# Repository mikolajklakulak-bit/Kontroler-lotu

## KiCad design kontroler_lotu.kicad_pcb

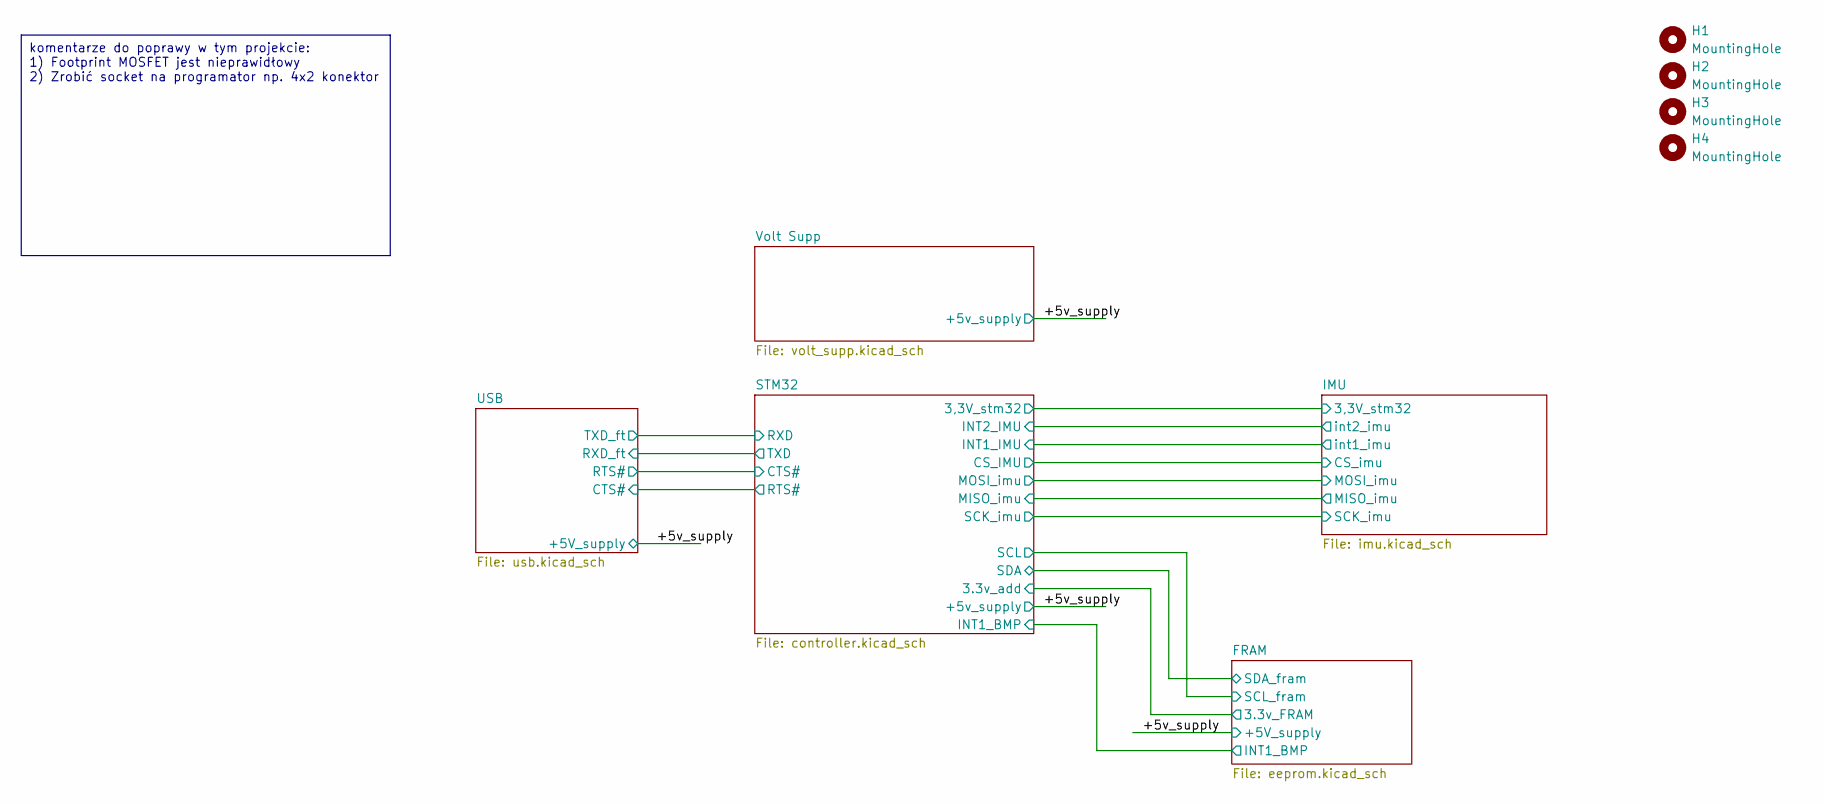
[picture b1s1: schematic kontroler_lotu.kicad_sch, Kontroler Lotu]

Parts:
H1, H2, H3, H4: MountingHole; MountingHole_3.2mm_M3_Pad

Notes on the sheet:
komentarze do poprawy w tym projekcie: 1) Footprint MOSFET jest nieprawidłowy 2) Zrobić socket na programator np. 4x2 konektor

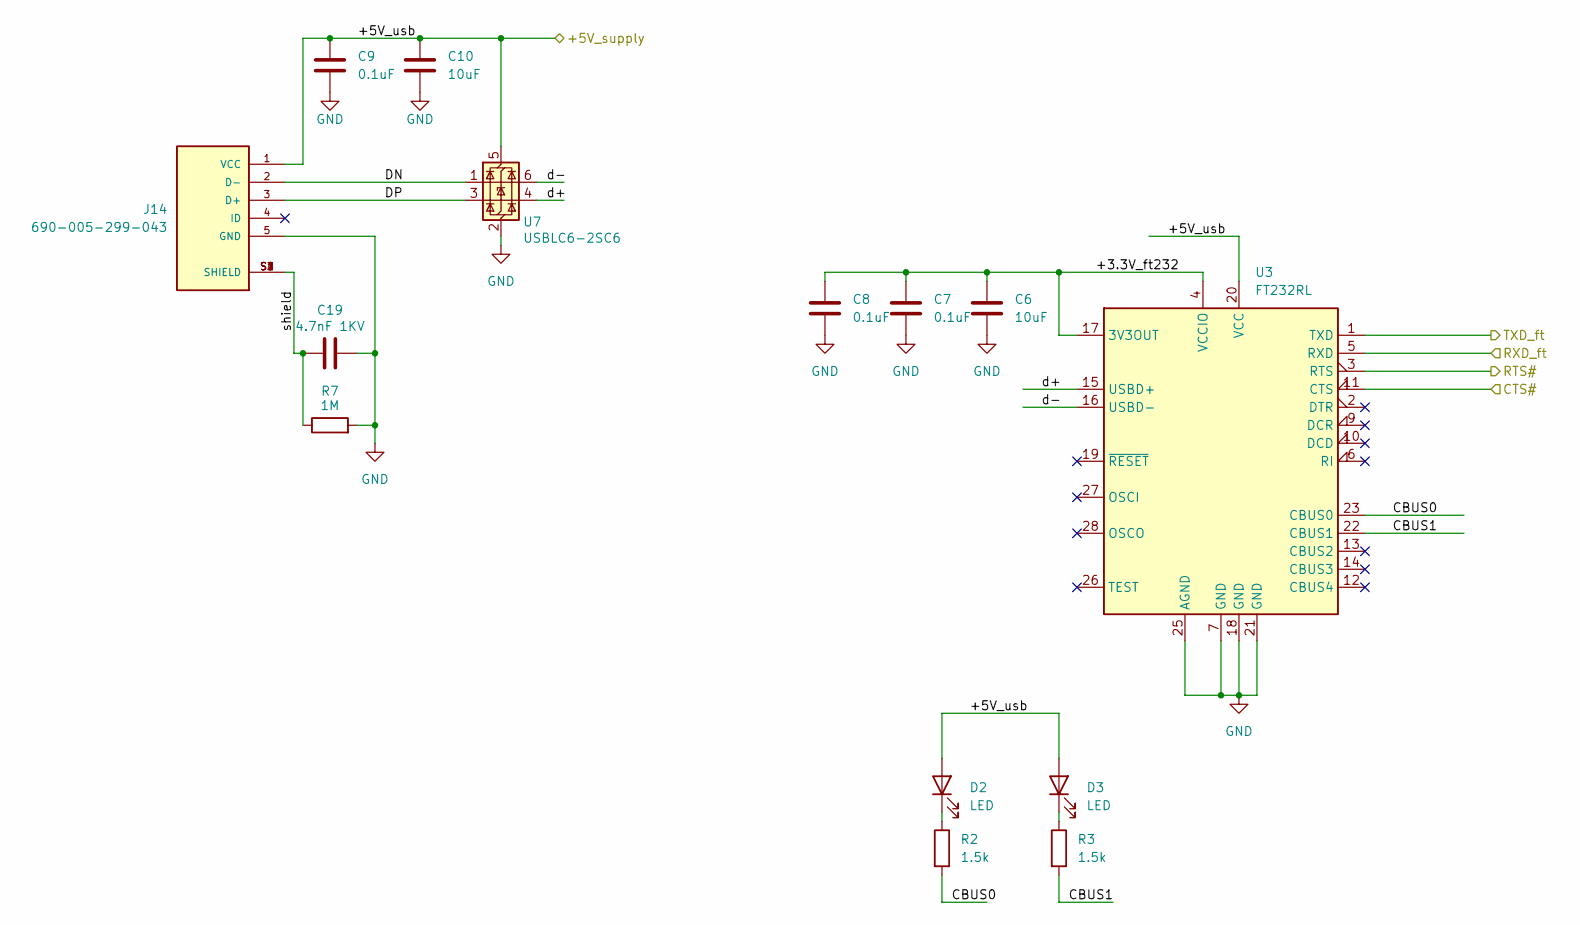
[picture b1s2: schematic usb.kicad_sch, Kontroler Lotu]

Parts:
C6, C10: 10uF; C_1206_3216Metric
C7, C8, C9: 0.1uF; C_0603_1608Metric
C19: 4.7nF 1KV; C_1210_3225Metric
D2, D3: LED; LED_0805_2012Metric
J14: 690-005-299-043; 690005299043; PARTREV 11; DigiKey_Part_Number 151-1206-2-ND
R2, R3: 1.5k; R_0603_1608Metric
R7: 1M; R_2512_6332Metric
U3: FT232RL; SSOP-28_5.3x10.2mm_P0.65mm
U7: USBLC6-2SC6; SOT-23-6

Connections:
/+5v_supply: C9.1, C10.1, D2.2 (A), D3.2 (A), J14.1 (VCC), U3.20 (VCC), U7.5 (VBUS); also elsewhere on the board
/STM32/CTS#: U3.3 (RTS); also elsewhere on the board
/STM32/RTS#: U3.11 (CTS); also elsewhere on the board
/STM32/RXD: U3.1 (TXD); also elsewhere on the board
/STM32/TXD: U3.5 (RXD); also elsewhere on the board
/USB/+3.3V_ft232: C6.1, C7.1, C8.1, U3.4 (VCCIO), U3.17 (3V3OUT)
/USB/CBUS0: R2.2, U3.23 (CBUS0)
/USB/CBUS1: R3.2, U3.22 (CBUS1)
/USB/DN: J14.2 (D-), U7.1 (I/O1)
/USB/DP: J14.3 (D+), U7.3 (I/O2)
/USB/d+: U3.15 (USBD+), U7.4 (I/O2)
/USB/d-: U3.16 (USBD-), U7.6 (I/O1)
/USB/shield: C19.1, J14.S1 (SHIELD), J14.S2 (SHIELD), J14.S3 (SHIELD), J14.S4 (SHIELD), R7.1
GND: C6.2, C7.2, C8.2, C9.2, C10.2, C19.2, J14.5 (GND), R7.2, U3.7 (GND), U3.18 (GND), U3.21 (GND), U3.25 (AGND), U7.2 (GND); also elsewhere on the board
unnamed: D2.1 (K), R2.1
unnamed: D3.1 (K), R3.1

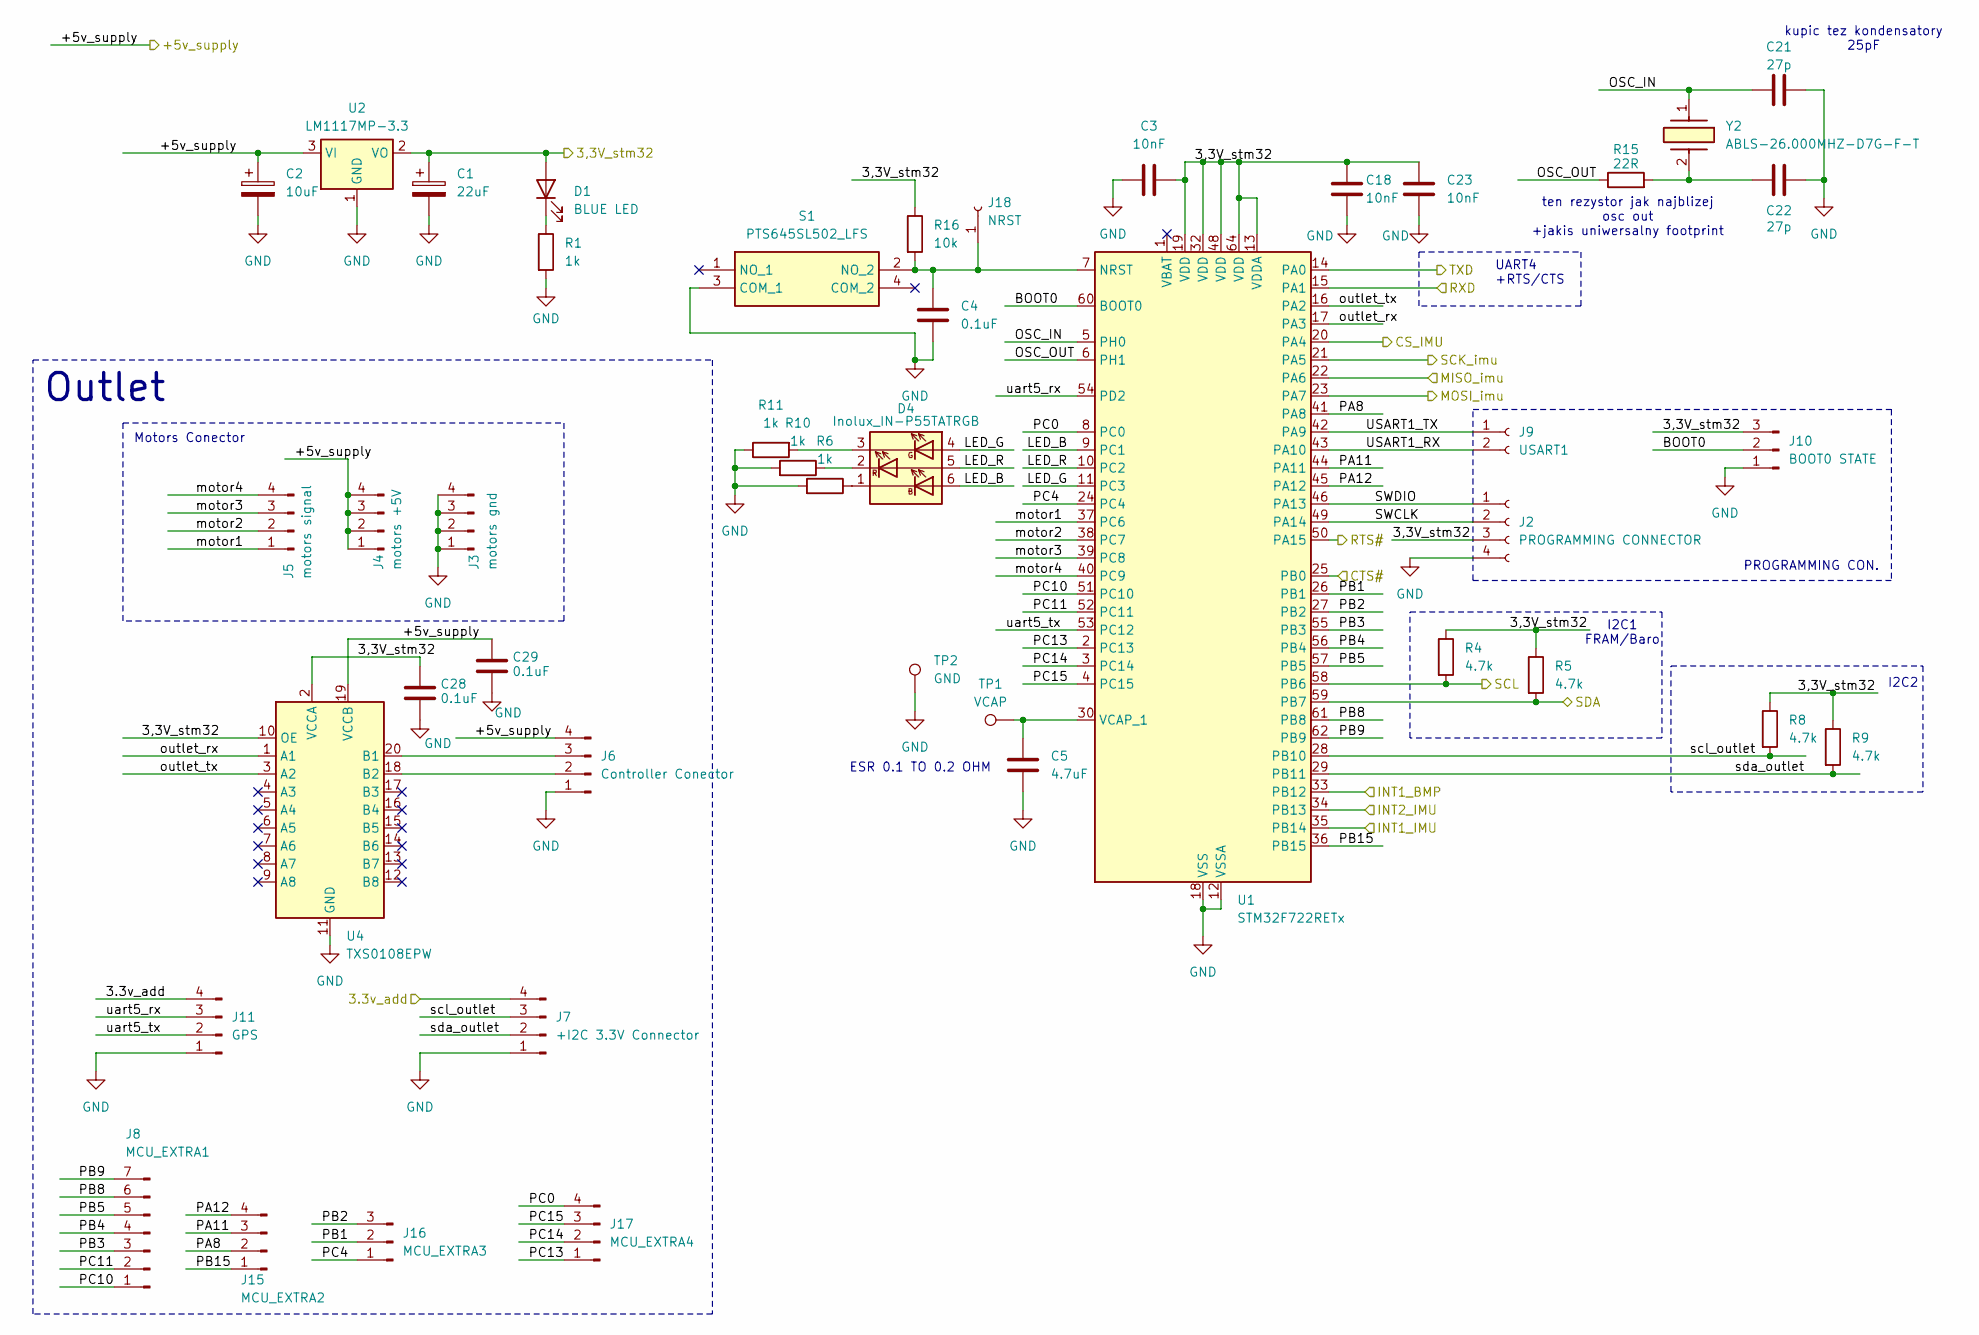
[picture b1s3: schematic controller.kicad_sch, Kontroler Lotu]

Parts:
C1: 22uF; CP_EIA-3528-12_Kemet-T
C2: 10uF; C_1206_3216Metric
C3, C18, C23: 10nF; C_0603_1608Metric
C4, C28, C29: 0.1uF; C_0603_1608Metric
C5: 4.7uF; C_0603_1608Metric
C21, C22: 27p; C_0603_1608Metric
D1: BLUE LED; LED_0805_2012Metric
D4: Inolux_IN-P55TATRGB; LED_Inolux_IN-P55TATRGB_PLCC6_5.0x5.5mm_P1.8mm
J2: PROGRAMMING CONNECTOR; PinHeader_1x04_P2.54mm_Vertical
J3: motors gnd; PinHeader_1x04_P2.54mm_Vertical
J4: motors +5V; PinHeader_1x04_P2.54mm_Vertical
J5: motors signal; PinHeader_1x04_P2.54mm_Vertical
J6: Controller Conector; PinHeader_1x04_P2.54mm_Vertical
J7: +I2C 3.3V Connector; PinHeader_1x04_P2.54mm_Vertical
J8: MCU_EXTRA1; PinHeader_1x07_P2.54mm_Vertical
J9: USART1; PinHeader_1x02_P2.54mm_Vertical
J10: BOOT0 STATE; PinHeader_1x03_P2.54mm_Vertical
J11: GPS; PinHeader_1x04_P2.54mm_Vertical
J15: MCU_EXTRA2; PinHeader_1x04_P2.54mm_Vertical
J16: MCU_EXTRA3; PinHeader_1x03_P2.54mm_Vertical
J17: MCU_EXTRA4; PinHeader_1x04_P2.54mm_Vertical
J18: NRST; PinHeader_1x01_P2.54mm_Vertical
R1, R6, R10, R11: 1k; R_0603_1608Metric
R4, R5, R8, R9: 4.7k; R_0603_1608Metric
R15: 22R; R_0603_1608Metric
R16: 10k; R_0603_1608Metric
S1: PTS645SL502_LFS; PTS645SL502LFS; Manufacturer_Part_Number PTS645SL502 LFS
TP1: VCAP; TestPoint_Keystone_5015_Micro-Minature
TP2: GND; TestPoint_Keystone_5015_Micro-Minature
U1: STM32F722RETx; LQFP-64_10x10mm_P0.5mm
U2: LM1117MP-3.3; SOT-223-3_TabPin2
U4: TXS0108EPW; TSSOP-20_4.4x6.5mm_P0.65mm
Y2: ABLS-26.000MHZ-D7G-F-T; ABLS; Manufacturer_Part_Number ABLS-26.000MHZ-D7G-F-T

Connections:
/+5v_supply: C2.1, C29.1, J4.1, J4.2, J4.3, J4.4, J6.4, U2.3 (VI), U4.19 (VCCB); also elsewhere on the board
/FRAM/3,3V_fram: J7.4, J11.4; also elsewhere on the board
/FRAM/INT1_BMP: U1.33 (PB12); also elsewhere on the board
/FRAM/SCL_fram: R4.2, U1.58 (PB6); also elsewhere on the board
/FRAM/SDA_fram: R5.2, U1.59 (PB7); also elsewhere on the board
/IMU/3,3V_imu: C1.1, C3.2, C18.2, C23.2, C28.1, D1.2 (A), J2.3, J10.3, R4.1, R5.1, R8.1, R9.1, R16.1, U1.13 (VDDA), U1.19 (VDD), U1.32 (VDD), U1.48 (VDD), U1.64 (VDD), U2.2 (VO), U4.2 (VCCA), U4.10 (OE); also elsewhere on the board
/IMU/CS_imu: U1.20 (PA4); also elsewhere on the board
/IMU/MISO_imu: U1.22 (PA6); also elsewhere on the board
/IMU/MOSI_imu: U1.23 (PA7); also elsewhere on the board
/IMU/SCK_imu: U1.21 (PA5); also elsewhere on the board
/IMU/int1_imu: U1.35 (PB14); also elsewhere on the board
/IMU/int2_imu: U1.34 (PB13); also elsewhere on the board
/STM32/BOOT0: J10.2, U1.60 (BOOT0)
/STM32/CTS#: U1.25 (PB0); also elsewhere on the board
/STM32/LED_B: D4.6 (AB), U1.9 (PC1)
/STM32/LED_G: D4.4 (AG), U1.11 (PC3)
/STM32/LED_R: D4.5 (AR), U1.10 (PC2)
/STM32/OSC_IN: C21.1, U1.5 (PH0), Y2.1
/STM32/OSC_OUT: R15.1, U1.6 (PH1)
/STM32/PA8: J15.2, U1.41 (PA8)
/STM32/PA11: J15.3, U1.44 (PA11)
/STM32/PA12: J15.4, U1.45 (PA12)
/STM32/PB1: J16.2, U1.26 (PB1)
/STM32/PB2: J16.3, U1.27 (PB2)
/STM32/PB3: J8.3, U1.55 (PB3)
/STM32/PB4: J8.4, U1.56 (PB4)
/STM32/PB5: J8.5, U1.57 (PB5)
/STM32/PB8: J8.6, U1.61 (PB8)
/STM32/PB9: J8.7, U1.62 (PB9)
/STM32/PB15: J15.1, U1.36 (PB15)
/STM32/PC0: J17.4, U1.8 (PC0)
/STM32/PC4: J16.1, U1.24 (PC4)
/STM32/PC10: J8.1, U1.51 (PC10)
/STM32/PC11: J8.2, U1.52 (PC11)
/STM32/PC13: J17.1, U1.2 (PC13)
/STM32/PC14: J17.2, U1.3 (PC14)
/STM32/PC15: J17.3, U1.4 (PC15)
/STM32/RTS#: U1.50 (PA15); also elsewhere on the board
/STM32/RXD: U1.15 (PA1); also elsewhere on the board
/STM32/SWCLK: J2.2, U1.49 (PA14)
/STM32/SWDIO: J2.1, U1.46 (PA13)
/STM32/TXD: U1.14 (PA0); also elsewhere on the board
/STM32/USART1_RX: J9.2, U1.43 (PA10)
/STM32/USART1_TX: J9.1, U1.42 (PA9)
/STM32/motor1: J5.1, U1.37 (PC6)
/STM32/motor2: J5.2, U1.38 (PC7)
/STM32/motor3: J5.3, U1.39 (PC8)
/STM32/motor4: J5.4, U1.40 (PC9)
/STM32/outlet_rx: U1.17 (PA3), U4.1 (A1)
/STM32/outlet_tx: U1.16 (PA2), U4.3 (A2)
/STM32/scl_outlet: J7.3, R8.2, U1.28 (PB10)
/STM32/sda_outlet: J7.2, R9.2, U1.29 (PB11)
/STM32/uart5_rx: J11.3, U1.54 (PD2)
/STM32/uart5_tx: J11.2, U1.53 (PC12)
GND: C1.2, C2.2, C3.1, C4.2, C5.2, C18.1, C21.2, C22.2, C23.1, C28.2, C29.2, J2.4, J3.1, J3.2, J3.3, J3.4, J6.1, J7.1, J10.1, J11.1, R1.2, R6.2, R10.2, R11.1, S1.3 (COM_1), TP2.1, U1.12 (VSSA), U1.18 (VSS), U1.31 (VSS), U1.47 (VSS), U1.63 (VSS), U2.1 (GND), U4.11 (GND); also elsewhere on the board
unnamed: C22.1, R15.2, Y2.2
unnamed: D1.1 (K), R1.1
unnamed: D4.1 (KB), R6.1
unnamed: D4.3 (KG), R11.2
unnamed: D4.2 (KR), R10.1
unnamed: J6.2, U4.18 (B2)
unnamed: J6.3, U4.20 (B1)
unnamed: C4.1, J18.1, R16.2, S1.2 (NO_2), U1.7 (NRST)
unnamed: C5.1, TP1.1, U1.30 (VCAP_1)

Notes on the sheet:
UART4 +RTS/CTS
kupic tez kondensatory 25pF
ten rezystor jak najblizej osc out +jakis uniwersalny footprint
Outlet
PROGRAMMING CON.
I2C1 FRAM/Baro
Motors Conector
I2C2
ESR 0.1 TO 0.2 OHM

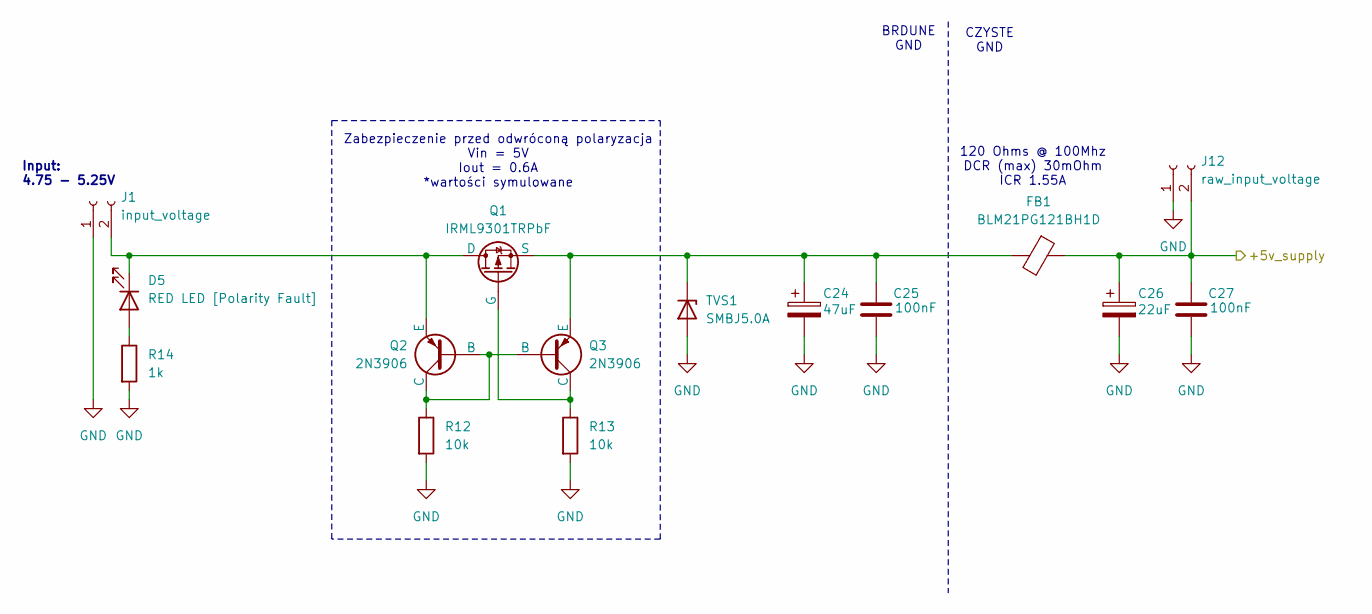
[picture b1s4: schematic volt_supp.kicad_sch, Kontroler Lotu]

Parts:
C24: 47uF; CP_EIA-3528-12_Kemet-T
C25, C27: 100nF; C_0603_1608Metric
C26: 22uF; CP_EIA-3528-12_Kemet-T
D5: RED LED [Polarity Fault]; LED_0805_2012Metric
FB1: BLM21PG121BH1D; L_0805_2012Metric_Pad1.15x1.40mm_HandSolder
J1: input_voltage; PinSocket_1x02_P2.54mm_Vertical
J12: raw_input_voltage; PinSocket_1x02_P2.54mm_Vertical
Q1: IRML9301TRPbF; SOT-23
Q2, Q3: 2N3906; TO-92L_Inline
R12, R13: 10k; R_0603_1608Metric
R14: 1k; R_0603_1608Metric
TVS1: SMBJ5.0A; D_SMB_Handsoldering

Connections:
/+5v_supply: C26.1, C27.1, FB1.1, J12.2; also elsewhere on the board
GND: C24.2, C25.2, C26.2, C27.2, J1.1, J12.1, R12.2, R13.2, R14.2, TVS1.2 (A); also elsewhere on the board
unnamed: D5.2 (A), R14.1
unnamed: D5.1 (K), J1.2, Q1.1 (D), Q2.3 (E)
unnamed: Q1.2 (G), Q3.1 (C), R13.1
unnamed: C24.1, C25.1, FB1.2, Q1.3 (S), Q3.3 (E), TVS1.1 (K)
unnamed: Q2.1 (C), Q2.2 (B), Q3.2 (B), R12.1

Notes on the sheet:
Zabezpieczenie przed odwróconą polaryzacja Vin = 5V Iout = 0.6A *wartości symulowane
CZYSTE GND
Input: 4.75 - 5.25V
BRDUNE GND
120 Ohms @ 100Mhz DCR (max) 30mOhm ICR 1.55A

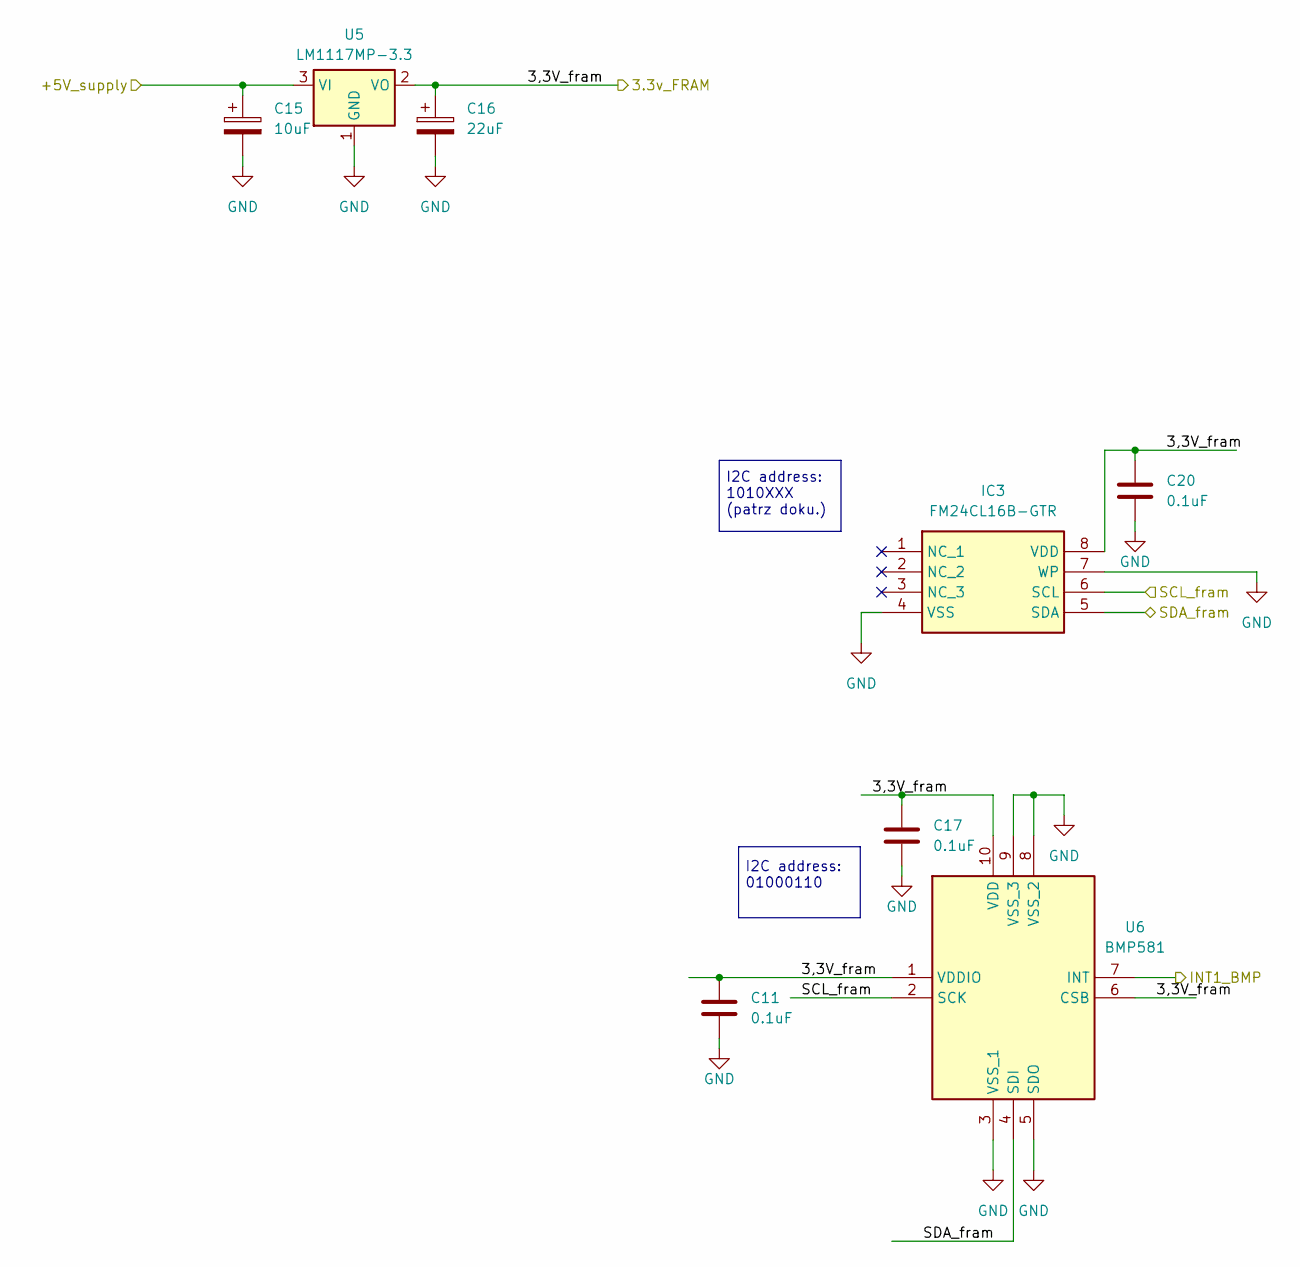
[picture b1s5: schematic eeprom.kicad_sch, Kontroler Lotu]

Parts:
C11, C17, C20: 0.1uF; C_0603_1608Metric
C15: 10uF; C_1206_3216Metric
C16: 22uF; CP_EIA-3528-12_Kemet-T
IC3: FM24CL16B-GTR; SOIC127P602X173-8N; Manufacturer_Part_Number FM24CL16B-GTR
U5: LM1117MP-3.3; SOT-223-3_TabPin2
U6: BMP581; Mouser Part Number 262-BMP581

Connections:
/+5v_supply: C15.1, U5.3 (VI); also elsewhere on the board
/FRAM/3,3V_fram: C11.1, C16.1, C17.1, C20.1, IC3.8 (VDD), U5.2 (VO), U6.1 (VDDIO), U6.6 (CSB), U6.10 (VDD); also elsewhere on the board
/FRAM/INT1_BMP: U6.7 (INT); also elsewhere on the board
/FRAM/SCL_fram: IC3.6 (SCL), U6.2 (SCK); also elsewhere on the board
/FRAM/SDA_fram: IC3.5 (SDA), U6.4 (SDI); also elsewhere on the board
GND: C11.2, C15.2, C16.2, C17.2, C20.2, IC3.4 (VSS), IC3.7 (WP), U5.1 (GND), U6.3 (VSS_1), U6.5 (SDO), U6.8 (VSS_2), U6.9 (VSS_3); also elsewhere on the board

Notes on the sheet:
I2C address: 01000110
I2C address: 1010XXX (patrz doku.)

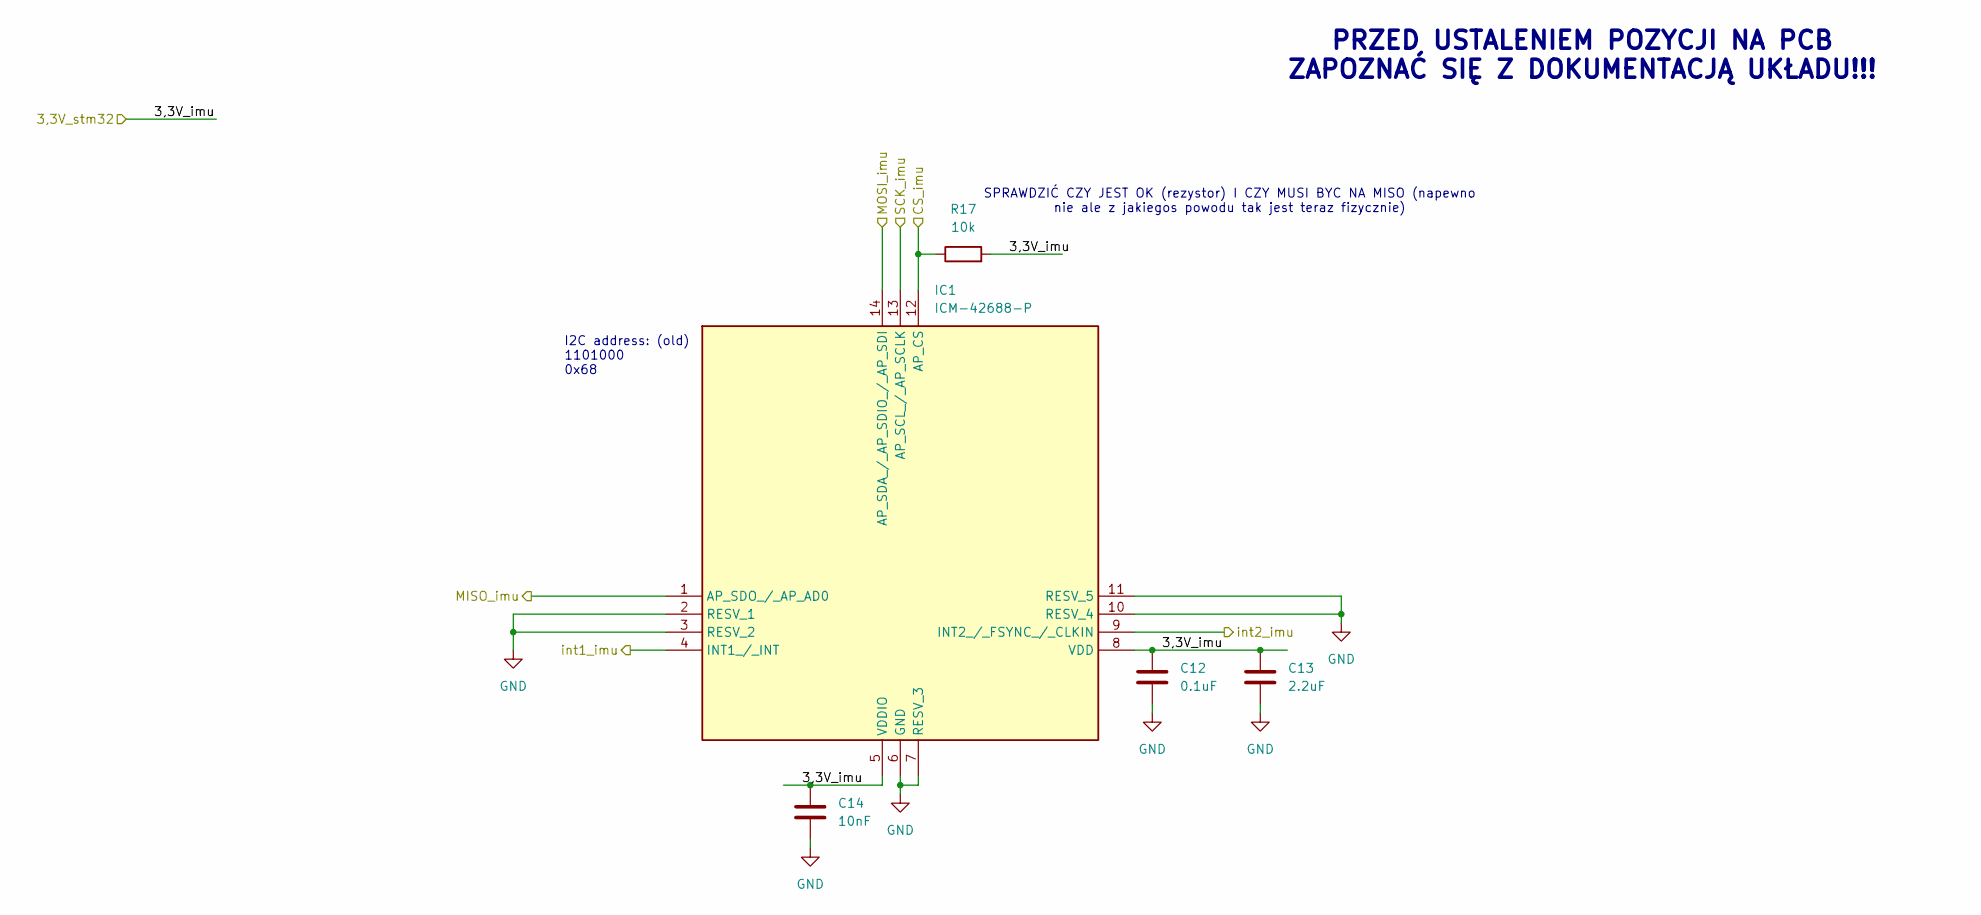
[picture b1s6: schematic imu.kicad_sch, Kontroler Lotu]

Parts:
C12: 0.1uF; C_0603_1608Metric
C13: 2.2uF; C_1206_3216Metric
C14: 10nF; C_0603_1608Metric
IC1: ICM-42688-P; IIM42352; Mouser Part Number 410-ICM-42688-P
R17: 10k; R_0603_1608Metric

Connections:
/IMU/3,3V_imu: C12.1, C13.1, C14.1, IC1.5 (VDDIO), IC1.8 (VDD), R17.2; also elsewhere on the board
/IMU/CS_imu: IC1.12 (AP_CS), R17.1; also elsewhere on the board
/IMU/MISO_imu: IC1.1 (AP_SDO_/_AP_AD0); also elsewhere on the board
/IMU/MOSI_imu: IC1.14 (AP_SDA_/_AP_SDIO_/_AP_SDI); also elsewhere on the board
/IMU/SCK_imu: IC1.13 (AP_SCL_/_AP_SCLK); also elsewhere on the board
/IMU/int1_imu: IC1.4 (INT1_/_INT); also elsewhere on the board
/IMU/int2_imu: IC1.9 (INT2_/_FSYNC_/_CLKIN); also elsewhere on the board
GND: C12.2, C13.2, C14.2, IC1.2 (RESV_1), IC1.3 (RESV_2), IC1.6 (GND), IC1.7 (RESV_3), IC1.10 (RESV_4), IC1.11 (RESV_5); also elsewhere on the board

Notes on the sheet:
PRZED USTALENIEM POZYCJI NA PCB ZAPOZNAĆ SIĘ Z DOKUMENTACJĄ UKŁADU!!!
SPRAWDZIĆ CZY JEST OK (rezystor) I CZY MUSI BYC NA MISO (napewno nie ale z jakiegos powodu tak jest teraz fizycznie)
I2C address: (old) 1101000 0x68

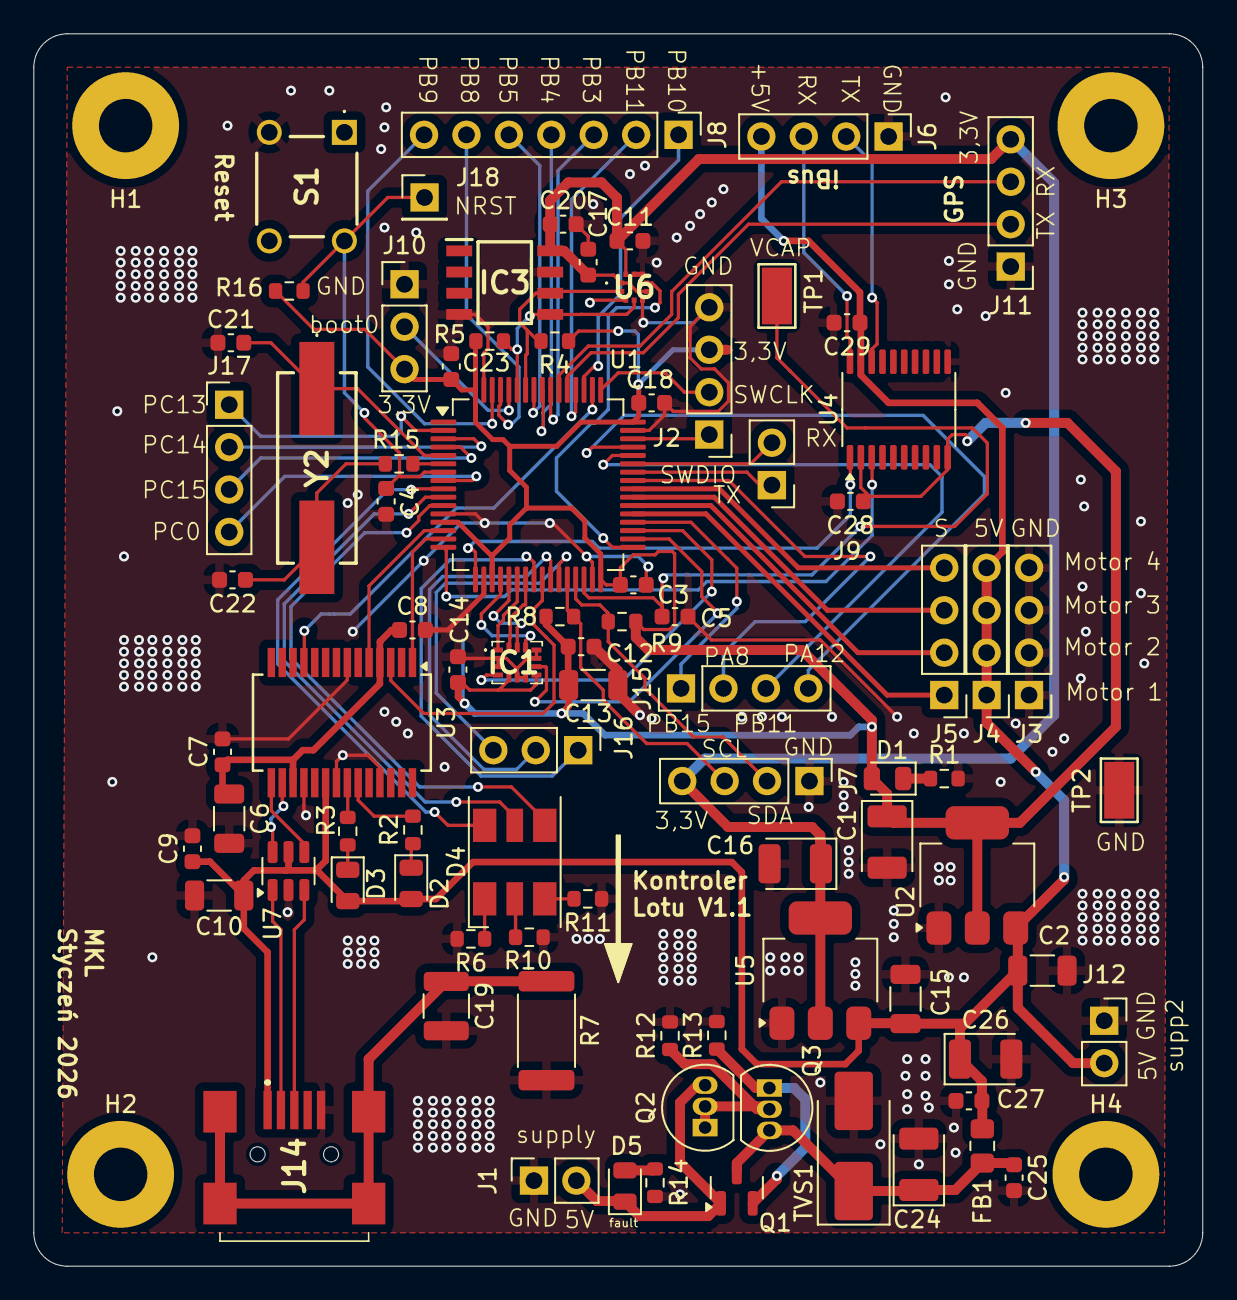
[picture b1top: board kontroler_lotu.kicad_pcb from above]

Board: 2 copper layers, 70.0 x 73.8 mm, 90 parts (1 on the bottom side), 79 nets.

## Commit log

2026-01-22 PCB pierwszy zrobiony prototyp
2026-01-24 Dodano układ wejściowy dla zasilania. Nie symulowano całości.
2026-01-25 Dodano brakujące footprinty do układu wejściowego i poprawiono SPI - zamieniono SCK <-> MISO (na poprawne)
2026-01-26 Zamieniono konwerter napięć na SMD. Zaktualizowano projekt PCB. Usunięto błedy - zostało część ostrzeżeń dotyczących nakładających się silk.
2026-04-21 dodano komentarze do projektu
